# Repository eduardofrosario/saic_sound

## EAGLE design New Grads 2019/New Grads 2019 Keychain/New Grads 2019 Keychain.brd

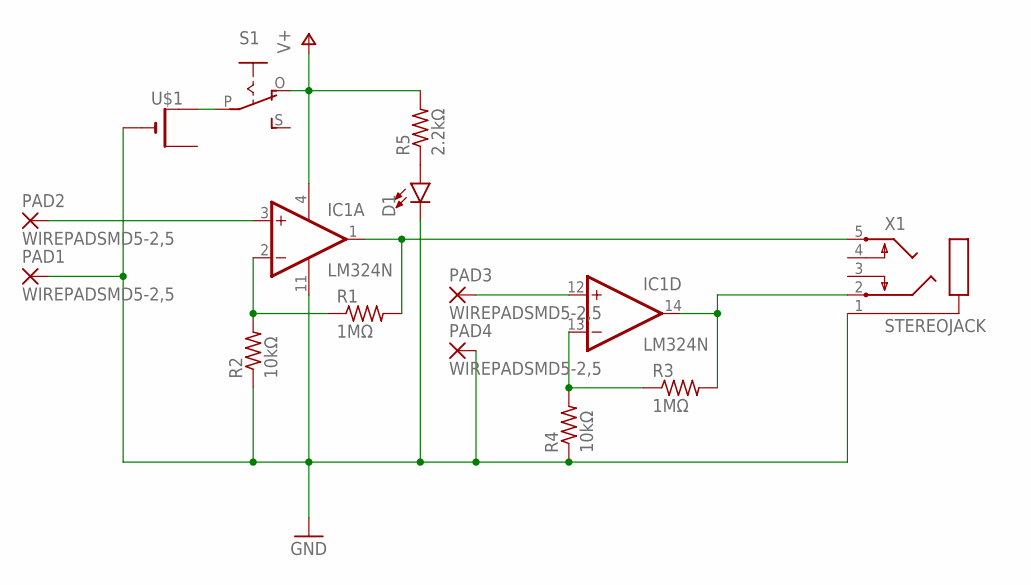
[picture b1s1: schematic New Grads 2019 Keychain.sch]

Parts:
D1: LED-3MM-NO_SILK; LED_3MM-NS
IC1: LM324N; DIL14
PAD1, PAD2, PAD3, PAD4: WIREPADSMD5-2,5; 5-2,5
R1, R3: 1MΩ; 0204/5
R2, R4: 10kΩ; 0204/5
R5: 2.2kΩ; 0204/5
S1: EG1218S; EG1218
U$1: CR1220THM; CR1220-THM
X1: STEREOJACK; STX3100

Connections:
GND: D1.K (C), IC1.11 (V-), PAD1.1, PAD4.1, R2.1, R4.1, U$1.-, X1.1
unnamed: IC1.1 (OUT), R1.2, X1.5
unnamed: IC1.2 (-IN), R1.1, R2.2
unnamed: S1.P, U$1.+1 (+)
unnamed: IC1.3 (+IN), PAD2.1
unnamed: IC1.13 (-IN), R3.1, R4.2
unnamed: IC1.14 (OUT), R3.2, X1.2
unnamed: IC1.12 (+IN), PAD3.1
unnamed: D1.A, R5.1
V+: IC1.4 (V+), R5.2, S1.O

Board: 2 copper layers, 14 parts (0 on the bottom side), 10 nets, no tracks yet.

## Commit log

2019-01-07 LM324 datasheet
    LM324 datasheet
2019-01-08 SoundKeychain2019
    Keychain 2019 Eagle Files

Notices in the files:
parts and their libraries:
SparkFun-LED: Licensing: Creative Commons ShareAlike 4.0 International - https://creativecommons.org/licenses/by-sa/4.0
